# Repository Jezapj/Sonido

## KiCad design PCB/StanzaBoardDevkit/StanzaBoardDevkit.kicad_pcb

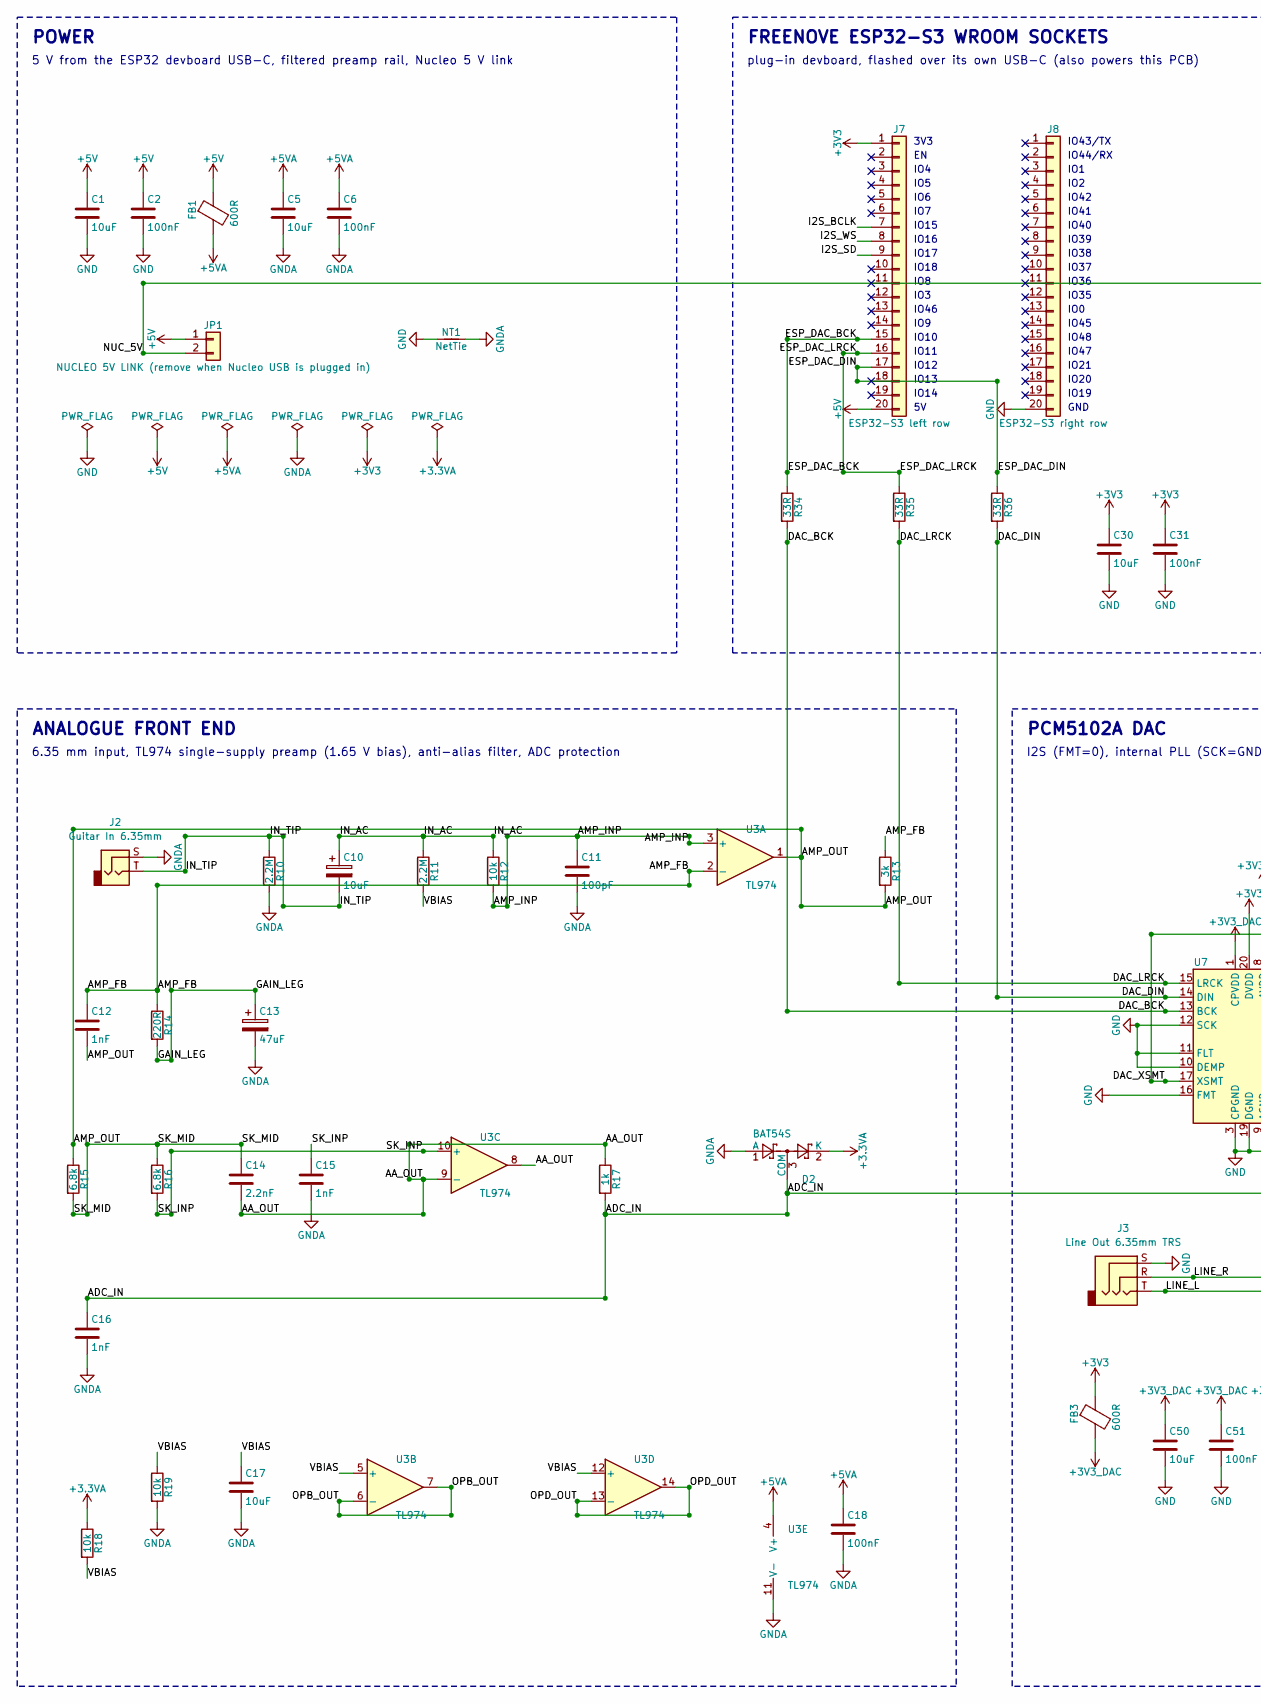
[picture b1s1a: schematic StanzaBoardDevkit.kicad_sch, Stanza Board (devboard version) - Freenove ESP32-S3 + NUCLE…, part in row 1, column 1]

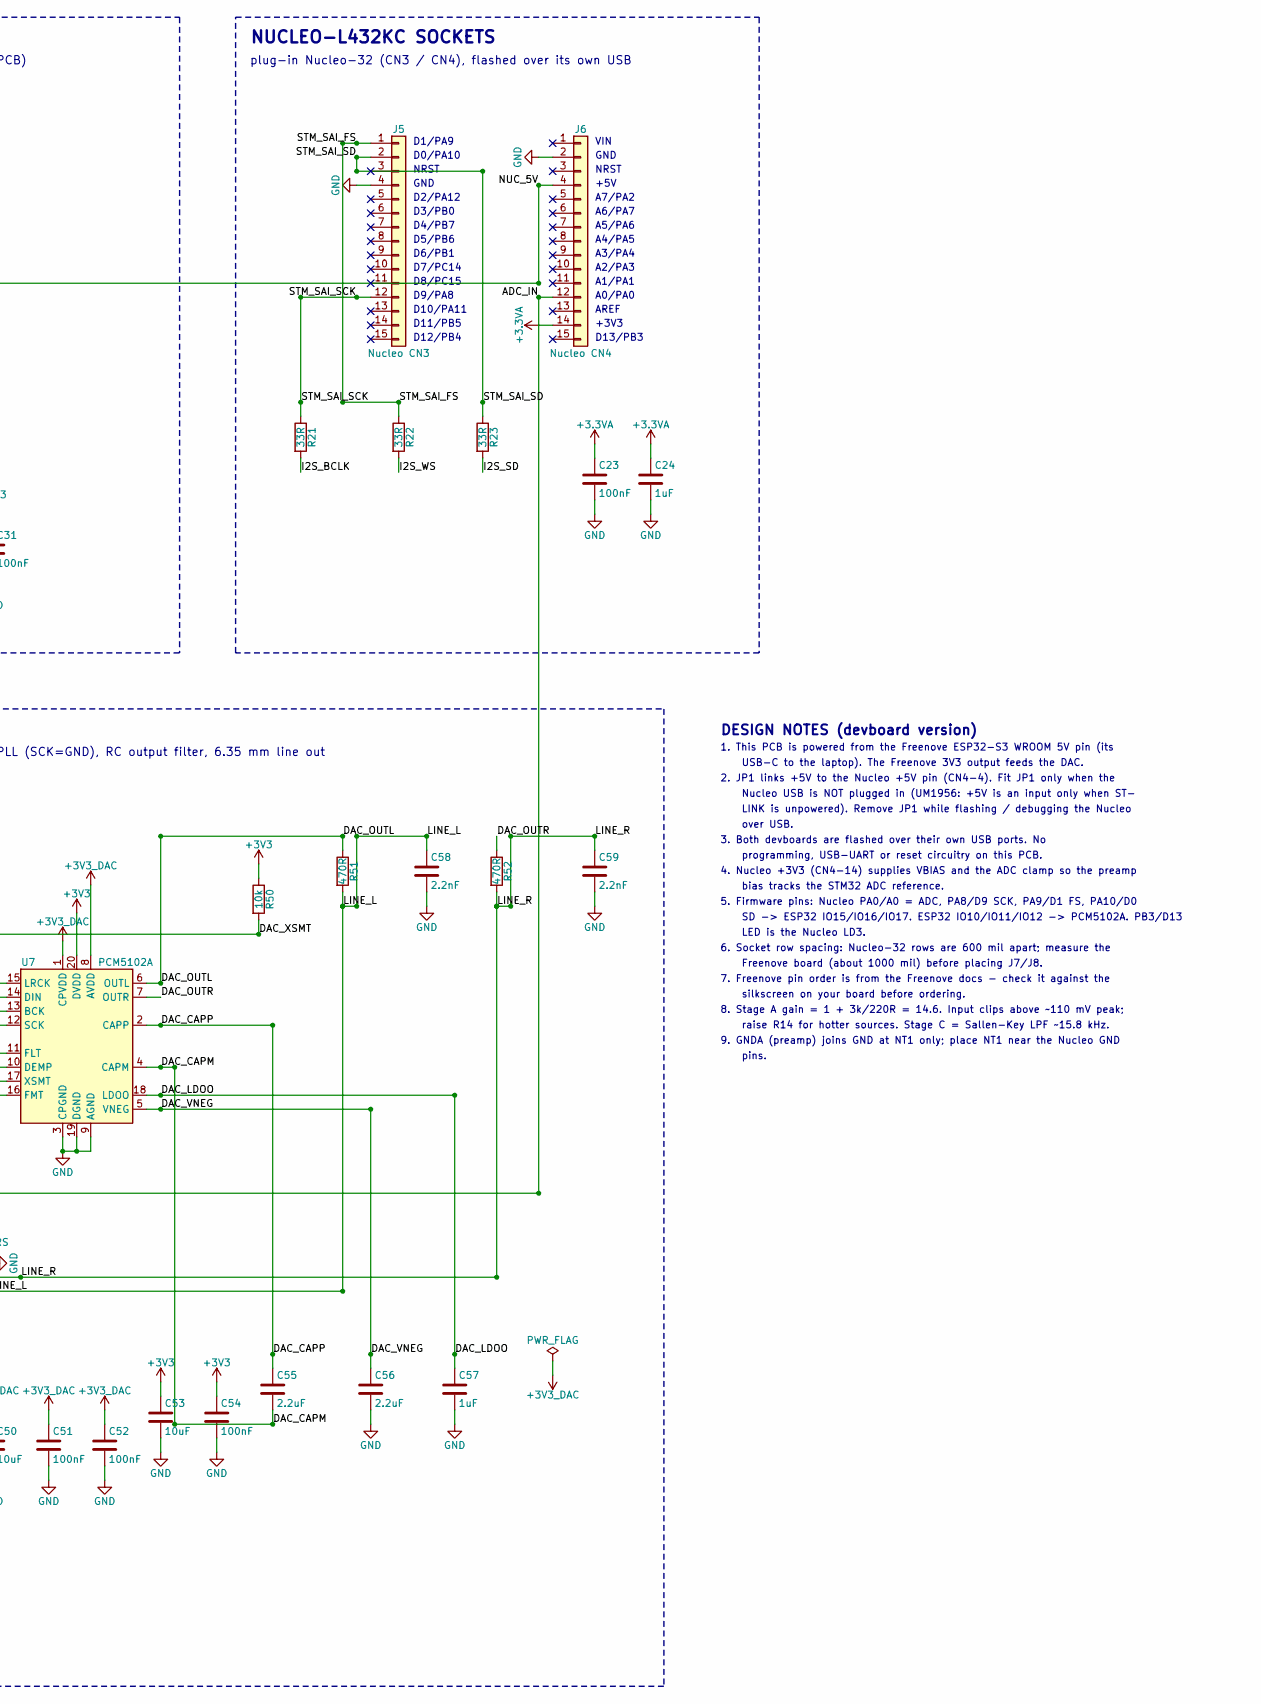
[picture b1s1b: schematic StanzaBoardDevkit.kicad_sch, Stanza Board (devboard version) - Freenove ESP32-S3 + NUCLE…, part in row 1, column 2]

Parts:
C1, C5, C17, C30, C50, C53: 10uF; C_0805_2012Metric
C2, C6, C18, C23, C31, C51, C52, C54: 100nF; C_0603_1608Metric
C10: 10uF; CP_Elec_5x5.4
C11: 100pF; C_0603_1608Metric
C12, C15, C16: 1nF; C_0603_1608Metric
C13: 47uF; CP_Elec_5x5.4
C14, C58, C59: 2.2nF; C_0603_1608Metric
C24, C57: 1uF; C_0603_1608Metric
C55, C56: 2.2uF; C_0603_1608Metric
D2: BAT54S; SOT-23
FB1, FB3: 600R; L_0603_1608Metric
J2: Guitar In 6.35mm; Jack_6.35mm_Neutrik_NMJ4HCD2_Horizontal
J3: Line Out 6.35mm TRS; Jack_6.35mm_Neutrik_NMJ6HCD2_Horizontal
J5: Nucleo CN3; PinSocket_1x15_P2.54mm_Vertical
J6: Nucleo CN4; PinSocket_1x15_P2.54mm_Vertical
J7: ESP32-S3 left row; PinSocket_1x20_P2.54mm_Vertical
J8: ESP32-S3 right row; PinSocket_1x20_P2.54mm_Vertical
JP1: NUCLEO 5V LINK (remove when Nucleo USB is plugged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; PinHeader_1x02_P2.54mm_Vertical
NT1: NetTie; NetTie-2_SMD_Pad0.5mm
R10, R11: 2.2M; R_0603_1608Metric
R12, R18, R19, R50: 10k; R_0603_1608Metric
R13: 3k; R_0603_1608Metric
R14: 220R; R_0603_1608Metric
R15, R16: 6.8k; R_0603_1608Metric
R17: 1k; R_0603_1608Metric
R21, R22, R23, R34, R35, R36: 33R; R_0603_1608Metric
R51, R52: 470R; R_0603_1608Metric
U3: TL974; SOIC-14_3.9x8.7mm_P1.27mm
U7: PCM5102A; TSSOP-20_4.4x6.5mm_P0.65mm

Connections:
+3V3: C30.1, C31.1, C53.1, C54.1, FB3.1, J7.1, R50.1, U7.20 (DVDD)
+3V3_DAC: C50.1, C51.1, C52.1, FB3.2, U7.1 (CPVDD), U7.8 (AVDD)
+5V: C1.1, C2.1, FB1.1, J7.20, JP1.1
+5VA: C5.1, C6.1, C18.1, FB1.2, U3.4 (V+)
/AMP_FB: C12.1, R13.1, R14.1, U3.2 (-)
/AMP_INP: C11.1, R12.2, U3.3 (+)
/AMP_OUT: C12.2, R13.2, R15.1, U3.1
/DAC_BCK: R34.2, U7.13 (BCK)
/DAC_CAPM: C55.2, U7.4 (CAPM)
/DAC_CAPP: C55.1, U7.2 (CAPP)
/DAC_DIN: R36.2, U7.14 (DIN)
/DAC_LDOO: C57.1, U7.18 (LDOO)
/DAC_LRCK: R35.2, U7.15 (LRCK)
/DAC_OUTL: R51.1, U7.6 (OUTL)
/DAC_OUTR: R52.1, U7.7 (OUTR)
/DAC_VNEG: C56.1, U7.5 (VNEG)
/DAC_XSMT: R50.2, U7.17 (XSMT)
/ESP_DAC_BCK: J7.15, R34.1
/ESP_DAC_DIN: J7.17, R36.1
/ESP_DAC_LRCK: J7.16, R35.1
/GAIN_LEG: C13.1, R14.2
/I2S_BCLK: J7.7, R21.2
/I2S_SD: J7.9, R23.2
/I2S_WS: J7.8, R22.2
/IN_AC: C10.1, R11.1, R12.1
/IN_TIP: C10.2, J2.T, R10.1
/LINE_L: C58.1, J3.T, R51.2
/LINE_R: C59.1, J3.R, R52.2
/NUC_5V: J6.4, JP1.2
/OPB_OUT: U3.6 (-), U3.7
/OPD_OUT: U3.13 (-), U3.14
/SK_INP: C15.1, R16.2, U3.10 (+)
/SK_MID: C14.1, R15.2, R16.1
/STM_SAI_FS: J5.1, R22.1
/STM_SAI_SCK: J5.12, R21.1
/STM_SAI_SD: J5.2, R23.1
/VBIAS: C17.1, R11.2, R18.2, R19.1, U3.5 (+), U3.12 (+)
GND: C1.2, C2.2, C23.2, C24.2, C30.2, C31.2, C50.2, C51.2, C52.2, C53.2, C54.2, C56.2, C57.2, C58.2, C59.2, J3.S, J5.4, J6.2, J8.20, NT1.1, U7.3 (CPGND), U7.9 (AGND), U7.10 (DEMP), U7.11 (FLT), U7.12 (SCK), U7.16 (FMT), U7.19 (DGND)

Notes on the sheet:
D1/PA9
D0/PA10
NRST
GND
D2/PA12
D3/PB0
D4/PB7
D5/PB6
D6/PB1
D7/PC14
D8/PC15
D9/PA8
D10/PA11
D11/PB5
D12/PB4
VIN
+5V
A7/PA2
A6/PA7
A5/PA6
A4/PA5
A3/PA4
A2/PA3
A1/PA1
A0/PA0
AREF
+3V3
D13/PB3
3V3
IO4
IO5
IO6
IO7
IO15
IO16
IO17
IO18
IO8
IO3
IO46

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
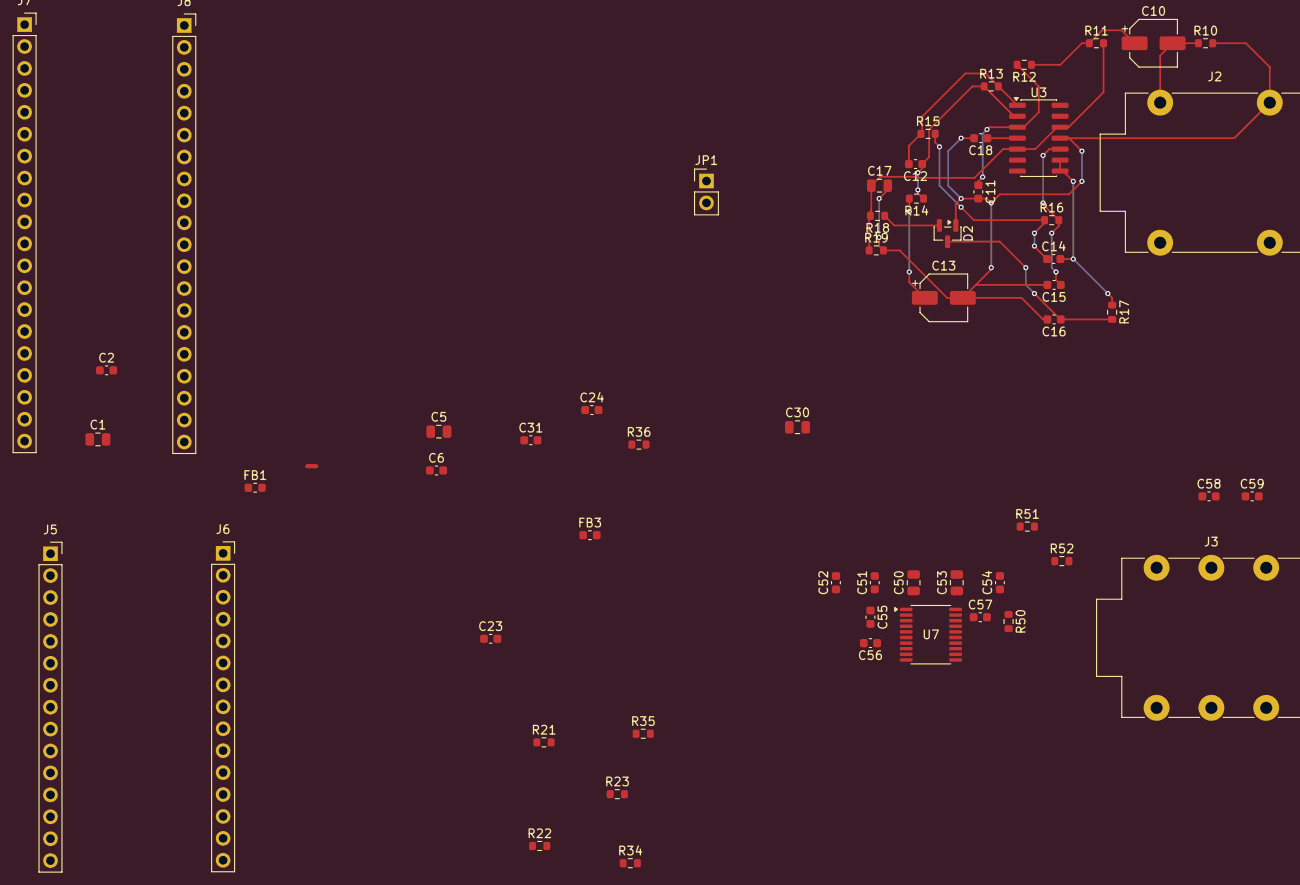
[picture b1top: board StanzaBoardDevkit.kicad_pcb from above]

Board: 2 copper layers, 59 parts (0 on the bottom side), 42 nets.

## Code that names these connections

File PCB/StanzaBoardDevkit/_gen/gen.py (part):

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wire(j6g, (j6g[0] + 7.62, j6g[1]))
pwr('GND', j6g[0] + 7.62, j6g[1])
wire(j6_5v, (j6_5v[0] + 10.16, j6_5v[1]))
# NUC_5V continues from JP1: draw a wire along the top from JP1 pin2 to J6 pin4
jp2 = pxy('JP1', '2')
# route JP1-2 right then up/over to J6-4
ybus = 10.16
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c13a, c13b = pxy('C13', '1'), pxy('C13', '2')
r15a, r15b = pxy('R15', '1'), pxy('R15', '2')

# AMP_OUT spine
wire(u3o, (r13b[0], u3o[1]))
add_j(r13b[0], u3o[1])
wire((r13b[0], u3o[1]), r13b)
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wire((r13b[0], u3o[1]), (r15a[0], u3o[1]), r15a)
add_j(r15a[0], u3o[1])

# AMP_FB spine
wire(u3n, (r13a[0], u3n[1]), r13a)
add_j(r13a[0], u3n[1])
wire((r13a[0], u3n[1]), (r13a[0], c12a[1]), c12a)
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x_adc = 254.0
wire((dcom[0], r17b[1]), (x_adc, r17b[1]), (x_adc, j6adc[1]), j6adc)
add_j(dcom[0], r17b[1])
text('ADC_IN  (Nucleo A0/PA0)', x_adc + 1.27, r17b[1] - 2.54, 1.0)

# VBIAS
r18a, r18b = pxy('R18', '1'), pxy('R18', '2')
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pwr('GNDA', r19b[0], r19b[1] + G)
wire(c17b, (c17b[0], c17b[1] + G))
pwr('GNDA', c17b[0], c17b[1] + G)
# R11.2 down to VBIAS spine
yvb = r18b[1]
wire(r11b, (r11b[0], yvb))
add_j(r11b[0], yvb)
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    'Power symbols are still used for GND / rails (KiCad power ports). All audio and I2S nets are drawn as wires.',
    'JP1 is a series link from +5V to Nucleo CN4-4. Remove it while the Nucleo USB is plugged in.',
    'Freenove pin order is from the vendor docs; check silkscreen before ordering sockets.',
    'GNDA joins GND only at NT1. ADC_IN is wired to Nucleo A0/PA0 (J6 pin 12).',
]
for i, n in enumerate(notes):
    text(n, 15.24, 380.0 + i * 4.0, 1.27)
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
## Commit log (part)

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2026-02-17 Made base dsp with DC blocking
2026-02-21 Added Input to STM32 Stage functionality
2026-02-21 Added Guitar Circuit SPICE file
2026-02-21 Added STM32 to ESP32-S3 Stage
2026-02-28 First Working Sound Output from ESP to amp
2026-02-28 Unprocessed passthough done (very noisy)
2026-04-06 True Bypass Functionality Achieved
2026-04-06 Started PCB design
2026-04-07 Audio fixed to sound better, major clock desync fixed
2026-04-10 DSP Added with tested EQ and bypass
2026-04-14 Added UI setup via Tauri + Rust + React/TypeScript stack
2026-04-19 Added basic landing page with background and icons
2026-04-19 Added Main page via simple navigation
2026-04-21 Added grid background for the main screen and basic transition animations in navigation
2026-04-22 Added Main page layout cards
2026-04-26 Fixed Dashboard Spacing
2026-04-26 Added Circular user text and labeled dashboard cards
2026-04-29 Added 3D Object to main dashboard
2026-04-29 Added inner content for the dashboard cards
2026-04-29 Added DSP pedal gallery with temp images
2026-05-02 Added test waveform visualiser and temp content for dashboard and preset cards
2026-05-04 Added dashboard card content and draft pedal card gallery content
2026-05-05 Added on/off toggle with indicators for pedals
2026-05-05 Added custom pedal images for pedal overlays
2026-05-06 Populated Profile and Settings in dock. Also prepared real audio stream to try
2026-05-08 Connect Hardware Audio stream to frontend with pedal support
2026-05-09 Added preset loading and saving. Also new pedal imgs
2026-05-10 Added fullscreen and light mode
2026-05-10 Added overdrive pedal and full fullscreen support
2026-05-11 Added pedal overlay light mode and better touch screen support
2026-05-11 Fixed linter issues to allow for release build
2026-05-11 Added typing text on landing and lightmode pedal images to use
2026-05-11 Updated light mode dock
2026-05-11 Added Dock changes coupling previous commit
2026-05-12 Populated profile and settings content, and added chorus pedal.
2026-05-14 Added looper functionality
2026-05-14 Added ESP side for looping
2026-05-14 fix: ensure Magic Bento cards don't collapse on small screens
    Added flex: 1 to .magic-bento-card__content and set a global min-height of 250px
    to .magic-bento-card. This prevents percentage-based children (like the
    Circular Gallery canvas) from collapsing to 0px height on small screen
    resolutions like 800x480.
2026-05-22 Added distortion, phaser and reverb pedal functionality
2026-05-26 Fixed the STM32 to ESP32 I2S drift issue via periodic circular wrap around corrections
2026-05-26 Added preset banks for quick changes and better storage interaction
2026-05-26 Added backing track functionality
2026-05-26 Added interim looping fix and moved web port to 3000 from 1420
2026-05-26 Adding setup adjustments (PreAmp and STM32)
2026-06-04 Reduced latency for live monitor and resized pedal name labels
2026-06-06 Temp looping via live monitor added
2026-06-07 Added keyboard controls for preset selection
